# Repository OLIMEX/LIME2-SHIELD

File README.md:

# LIME2-SHIELD
Shield for A20-OLinuXino-LIME2 which adds Audio, CAN, microSD-card, 2x UEXT, CAN

Product page: https://www.olimex.com/Products/OLinuXino/A20/LIME2-SHIELD/open-source-hardware

## Licensee
* Hardware is released under CERN Open Hardware Licence Version 2 -
Strongly Reciprocal
* Software is released under GPL3 Licensee
* Documentation is released under CC BY-SA 3.0

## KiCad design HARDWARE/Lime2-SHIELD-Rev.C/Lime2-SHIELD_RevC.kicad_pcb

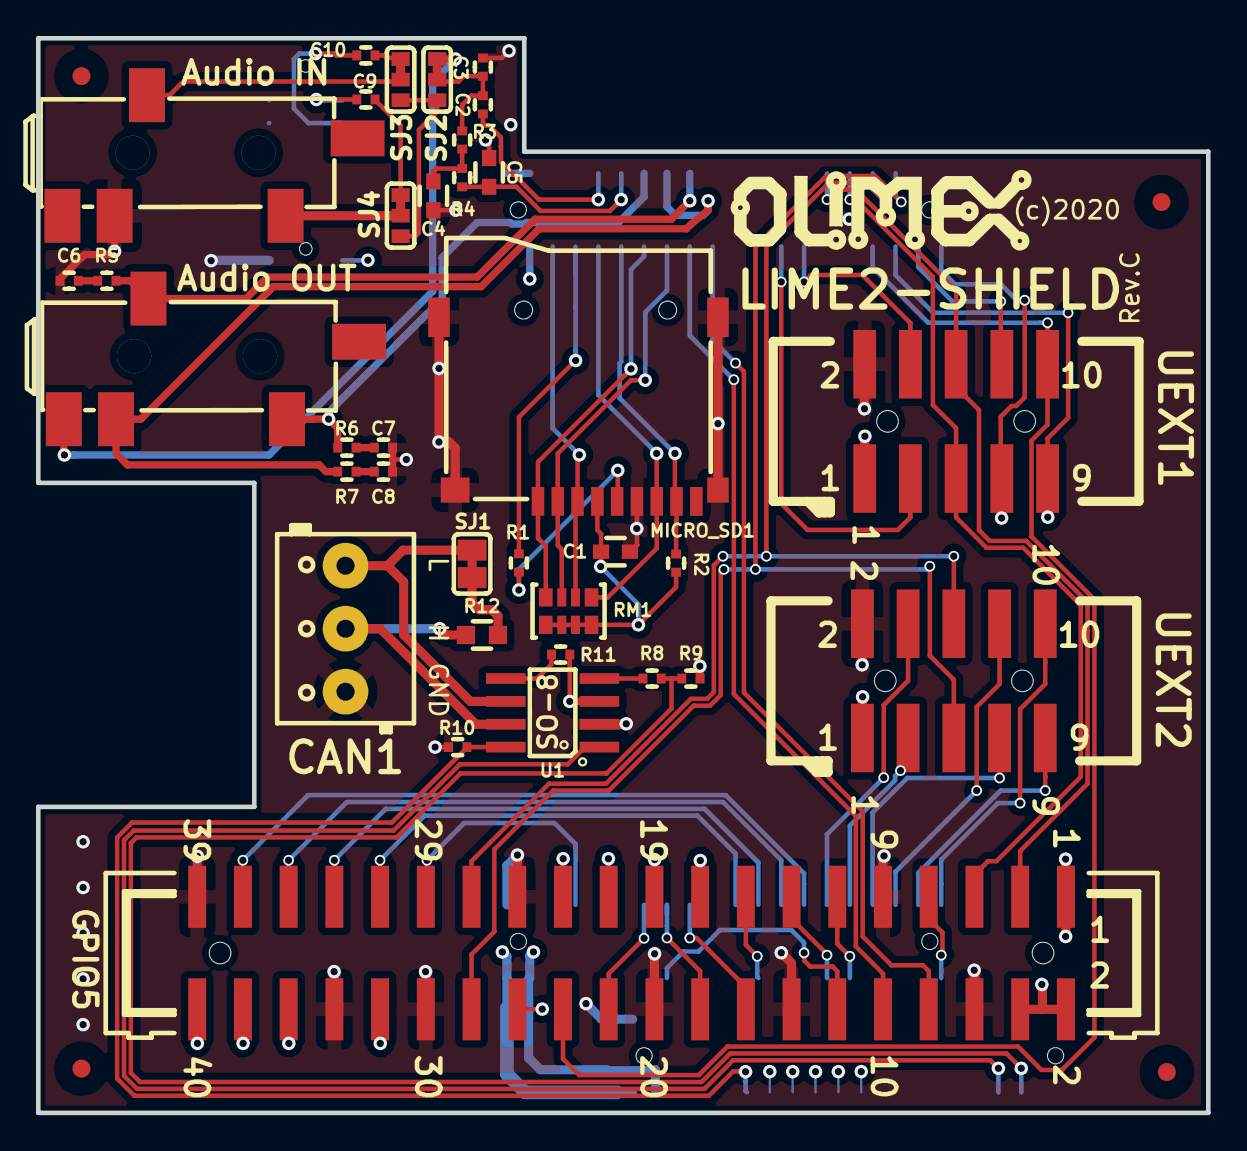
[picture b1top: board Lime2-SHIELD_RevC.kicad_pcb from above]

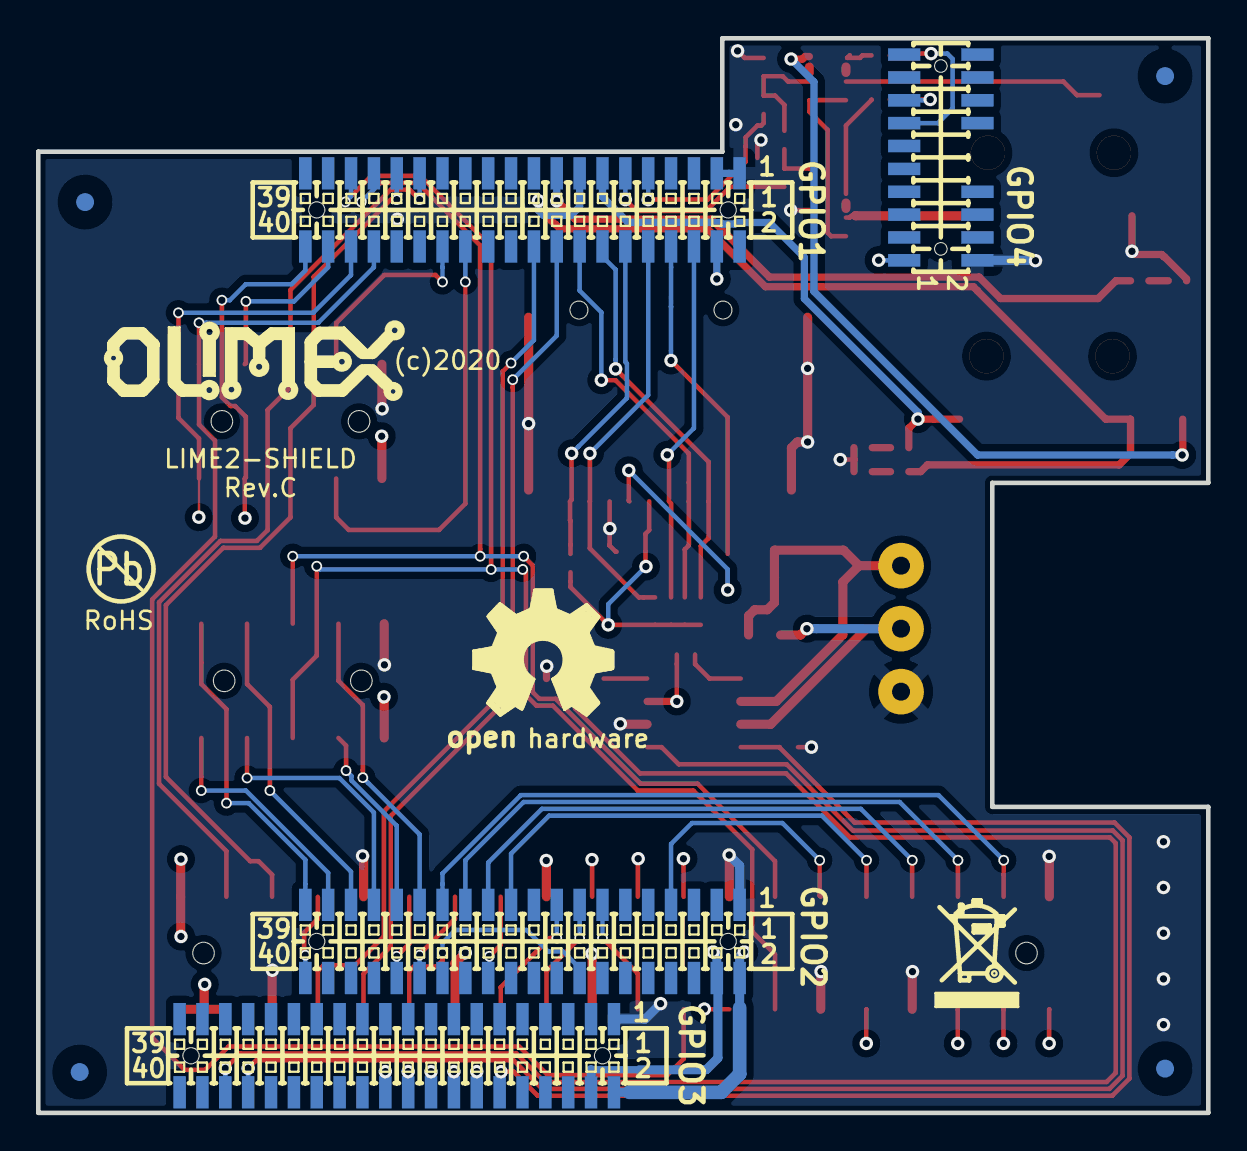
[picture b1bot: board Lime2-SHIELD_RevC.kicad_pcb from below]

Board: 4 copper layers, 65.0 x 59.7 mm, 47 parts (8 on the bottom side), 72 nets.

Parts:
AUDIO_JACK_5PIN1, AUDIO_JACK_5PIN2: PJ-W47S-05D2-LF_V2; PJ-W47S-05D2-LF_5PIN_V2
C1, C4, C5: 10uF; C_0603_5MIL_DWS
C2, C6, C7, C8, C9, C10: 100nF; C_0402_5MIL_DWS
C3: 1nF; C_0402_5MIL_DWS
CAN1: CON3; TB3-3.5mm
GPIO1, GPIO2, GPIO3: BH40S; GPH127SMT-02X20(PA-V16X-2X20-LF)_Drill_0.9mm
GPIO4: BH20S; GPCB127SMT-02X10(YA-V36P-2X10-LF)
GPIO5: BH40S; GBH-254-SMT-40_Shorten_Pads
MICRO_SD1: MICRO_SD(TFC-WPAPR-08); TFC-WPAPR-08
R1, R3, R4, R5, R6, R7: 22R; R_0402_5MIL_DWS
R2: 100K; R_0402_5MIL_DWS
R8, R10: 10K; R_0402_5MIL_DWS
R9: 22K; R_0402_5MIL_DWS
R11: n.a.; R_0402_5MIL_DWS
R12: 120R; R_0603_5MIL_DWS
RM1: RA1206_(4x0603)_100K; R_MATRIX_4_KICAD
Ref*: Val**; Fiducial1x3_transp
Ref*#2, Ref*#3, Ref*#4, Ref*#5, Ref*#6, Ref*#7, Ref*#8: Val**; Fiducial1x3_transp
SJ1: open; SJ_Closed
SJ2, SJ3, SJ4: SJ2W_Closed(1-2); SJ_2_SMALL_12_TIED
U1: SIT1050T; SO-8
UEXT1, UEXT2: BH10S; GBH-254-SMT-10_Smaller

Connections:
/+3.3V: C1.1, GPIO1.4, GPIO2.4, GPIO3.4, GPIO4.1, GPIO5.1, GPIO5.17, MICRO_SD1.4, R2.1, RM1.5, RM1.6, RM1.7, RM1.8, UEXT1.1, UEXT2.1
/+5V: GPIO2.2, GPIO3.2, GPIO5.2, GPIO5.4, R11.1, U1.3
/HPCOM: AUDIO_JACK_5PIN1.5, GPIO1.15, R7.2
/HPOUTL: AUDIO_JACK_5PIN1.2, GPIO1.13, R6.2
/HPOUTR: AUDIO_JACK_5PIN1.3, GPIO1.17, R5.2
/LINEINL: C9.2, GPIO4.15
/LINEINR: C10.2, GPIO4.13
/MICIN1: C2.1, GPIO1.9
/PB18_TWI1-SCL: GPIO1.35, GPIO5.28, UEXT2.5
/PB19_TWI1-SDA: GPIO1.33, GPIO5.27, UEXT2.6
/PB20_TWI2-SCL: GPIO1.31, GPIO5.5, UEXT1.5
/PB21_TWI2-SDA: GPIO1.29, GPIO5.3, UEXT1.6
/PC19_SPI2_CS0: GPIO1.34, GPIO5.24, UEXT1.10
/PC20_SPI2_CLK: GPIO1.36, GPIO5.23, UEXT1.9
/PC21_SPI2_MOSI: GPIO1.38, GPIO5.19, UEXT1.8
/PC22_SPI2_MISO: GPIO1.40, GPIO5.21, UEXT1.7
/PE1: GPIO2.7, GPIO5.29
/PE4: GPIO2.13, GPIO5.22
/PE5: GPIO2.15, GPIO5.18
/PE6: GPIO2.17, GPIO5.16
/PE8: GPIO2.21, GPIO5.31
/PE9: GPIO2.23, GPIO5.33
/PE10: GPIO2.25, GPIO5.35
/PE11: GPIO2.27, GPIO5.37
/PG0: GPIO1.6, MICRO_SD1.3, RM1.2
/PG1: GPIO1.8, R1.2
/PG2: GPIO1.10, MICRO_SD1.7, RM1.1
/PG3: GPIO1.12, MICRO_SD1.8, R2.2
/PG4: GPIO1.14, MICRO_SD1.1, RM1.4
/PG5: GPIO1.16, MICRO_SD1.2, RM1.3
/PG6_UART3TX: GPIO1.18, GPIO5.10
/PG7_UART3RX: GPIO1.20, GPIO5.8
/PG10_UART4TX: GPIO1.26, UEXT1.3
/PG11_UART4RX: GPIO1.28, UEXT1.4
/PH9_CANS: GPIO3.12, R10.1, U1.8
/PH10: GPIO3.14, GPIO5.40
/PH11: GPIO3.16, GPIO5.38
/PH12: GPIO3.18, GPIO5.36
/PH13: GPIO3.20, GPIO5.32
/PH14: GPIO3.22, GPIO5.26
/PH20_CANTX: GPIO3.34, U1.1
/PH21_CANRX: GPIO3.36, R8.2, R9.1
/PI3_PWM1: GPIO2.16, GPIO5.12
/PI7: GPIO2.24, GPIO5.15
/PI10: GPIO2.30, GPIO5.13
/PI11: GPIO2.32, GPIO5.11
/PI15: GPIO2.40, GPIO5.7
/PI16_SPI1_CS0: GPIO2.39, UEXT2.10
/PI17_SPI1_CLK: GPIO2.37, UEXT2.9
/PI18_SPI1_MOSI: GPIO2.35, UEXT2.8
/PI19_SPI1_MISO: GPIO2.33, UEXT2.7
/PI20_UART7TX: GPIO2.31, UEXT2.3
/PI21_UART7RX: GPIO2.29, UEXT2.4
/VMIC: C5.1, GPIO1.11, R4.1
GND: AUDIO_JACK_5PIN2.5, C1.2, C3.1, C4.2, C5.2, C6.1, C7.1, C8.1, CAN1.3, GPIO1.1, GPIO1.3, GPIO2.1, GPIO3.1, GPIO4.2, GPIO5.6, GPIO5.9, GPIO5.14, GPIO5.20, GPIO5.25, GPIO5.30, GPIO5.34, GPIO5.39, MICRO_SD1.6, MICRO_SD1.10, MICRO_SD1.11, MICRO_SD1.12, MICRO_SD1.13, R9.2, R10.2, U1.2, UEXT1.2, UEXT2.2
unnamed: AUDIO_JACK_5PIN1.1, SJ2.1
unnamed: AUDIO_JACK_5PIN2.2, SJ4.2
unnamed: AUDIO_JACK_5PIN2.3, SJ3.2
unnamed: C2.2, C3.2, R3.2, SJ2.2
unnamed: C4.1, R3.1, R4.2
unnamed: C6.2, R5.1
unnamed: C7.2, R6.1
unnamed: C8.2, R7.1
unnamed: C9.1, SJ4.1
unnamed: C10.1, SJ3.1
unnamed: CAN1.1, SJ1.1, U1.6
unnamed: CAN1.2, R12.2, U1.7
unnamed: MICRO_SD1.5, R1.1
unnamed: R8.1, U1.4
unnamed: R11.2, U1.5
unnamed: R12.1, SJ1.2
unnamed: SJ2.3, SJ3.3, SJ4.3

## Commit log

2020-07-09 upload Cad files, user manual
2020-07-09 schematic pdf

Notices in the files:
HARDWARE/Lime2-SHIELD-Rev.C/Lime2-SHIELD_RevC.kicad_pcb:
(c)2020
